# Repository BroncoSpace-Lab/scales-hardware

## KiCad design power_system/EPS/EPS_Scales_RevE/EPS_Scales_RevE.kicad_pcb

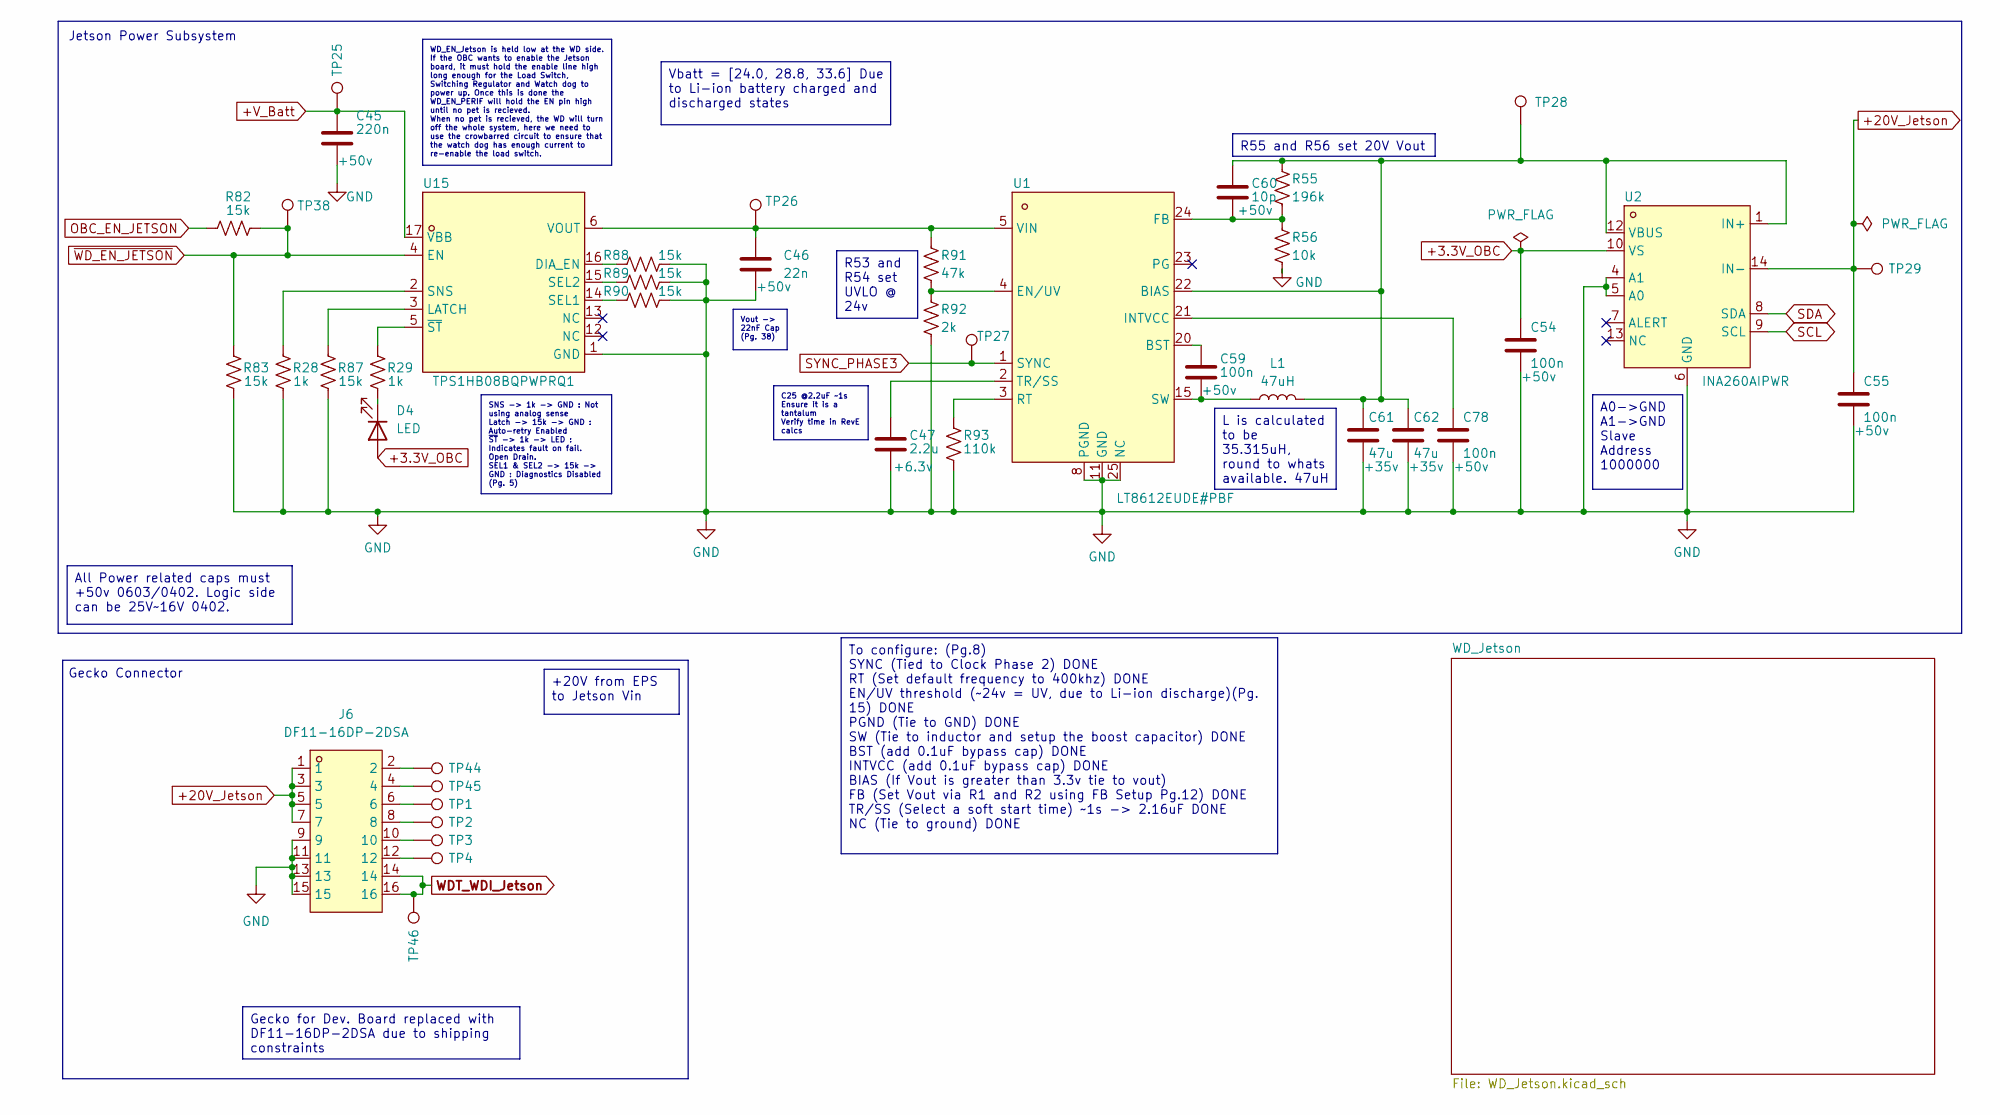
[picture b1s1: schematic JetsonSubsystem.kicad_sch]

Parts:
C45: 220n; C0402; Voltage Rating +50v; LCSC C5159775
C46: 22n; C0402; Voltage Rating +50v; LCSC C77023
C47: 2.2u; C0402; Voltage Rating +6.3v; LCSC C12530
C54, C55, C59, C78: 100n; C0402; Voltage Rating +50v; LCSC C85858
C60: 10p; C0402; Voltage Rating +50v; LCSC C1545
C61, C62: 47u; CAP-SMD_L7.3-W4.3-FD; Voltage Rating +35v; LCSC C87110
D4: LED; LED0603-RD_RED
J6: DF11-16DP-2DSA; CONN-TH_DF11-16DP-2DSA-08; LCSC Part C530981
L1: 47uH; IND-SMD_L10.7-W10.0_ETQP5MXXXX; LCSC C409637
R28, R29: 1k; R0402
R55: 196k; R0402; LCSC C2077051
R56: 10k; R0402; LCSC C25531
R82, R83, R87, R88, R89, R90: 15k; R0402; LCSC C114761
R91: 47k; R0402; LCSC C93943
R92: 2k; R0402; LCSC C60488
R93: 110k; R0402; LCSC C138065
TP1, TP2, TP3, TP4, TP25, TP26, TP27, TP28, TP29, TP38, TP44, TP45, TP46: TestPoint; TestPoint_Pad_1.0x1.0mm
U1: LT8612EUDE#PBF; QFN-28_L6.0-W3.0-P0.50-BL-EP; LCSC Part C580312
U2: INA260AIPWR; TSSOP-16_L5.0-W4.4-P0.65-LS6.4-BL-1; LCSC Part C2155885
U15: TPS1HB08BQPWPRQ1; HTSSOP-16_L5.0-W4.4-P0.65-LS6.4-TL-EP2.9; LCSC Part C3230075

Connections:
+3.3V_OBC: C54.1, D4.2 (A), U2.10 (VS); also elsewhere on the board
+20V_Jetson: C55.1, J6.1, J6.3, J6.5, J6.7, TP29.1, U2.14 (IN-); also elsewhere on the board
+V_Batt: C45.1, TP25.1, U15.17 (VBB); also elsewhere on the board
GND: C45.2, C46.2, C47.2, C54.2, C55.2, C61.2, C62.2, C78.2, J6.9, J6.11, J6.13, J6.15, R28.1, R56.2, R83.2, R87.2, R88.2, R89.2, R90.2, R92.2, R93.2, U1.8 (PGND), U1.11 (GND), U1.25 (NC), U2.4 (A1), U2.5 (A0), U2.6 (GND), U15.1 (GND); also elsewhere on the board
unnamed: D4.1 (K), R29.1
unnamed: J6.2, TP44.1
unnamed: J6.4, TP45.1
unnamed: J6.6, TP1.1
unnamed: J6.8, TP2.1
unnamed: J6.10, TP3.1
unnamed: J6.12, TP4.1
unnamed: C60.1, C61.1, C62.1, L1.2, R55.1, TP28.1, U1.22 (BIAS), U2.1 (IN+), U2.12 (VBUS)
unnamed: C59.1, U1.20 (BST)
unnamed: R91.2, R92.1, U1.4 (EN/UV)
unnamed: C60.2, R55.2, R56.1, U1.24 (FB)
unnamed: C78.1, U1.21 (INTVCC)
unnamed: R93.1, U1.3 (RT)
unnamed: C59.2, L1.1, U1.15 (SW)
unnamed: C47.1, U1.2 (TR/SS)
unnamed: C46.1, R91.1, TP26.1, U1.5 (VIN), U15.6 (VOUT)
unnamed: R88.1, U15.16 (DIA_EN)
unnamed: R87.1, U15.3 (LATCH)
unnamed: R90.1, U15.14 (SEL1)
unnamed: R89.1, U15.15 (SEL2)
unnamed: R28.2, U15.2 (SNS)
unnamed: R29.2, U15.5 (~ST)
OBC_EN_JETSON: R82.2; also elsewhere on the board
SCL: U2.9 (SCL); also elsewhere on the board
SDA: U2.8 (SDA); also elsewhere on the board
SYNC_PHASE3: TP27.1, U1.1 (SYNC); also elsewhere on the board
WDT_WDI_Jetson: J6.14, J6.16, TP46.1; also elsewhere on the board
~WD_EN_JETSON: R82.1, R83.1, TP38.1, U15.4 (EN); also elsewhere on the board

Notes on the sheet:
Jetson Power Subsystem
Gecko Connector
Gecko for Dev. Board replaced with DF11-16DP-2DSA due to shipping constraints
C25 @2.2uF ~1s Ensure it is a tantalum Verify time in RevE calcs
To configure: (Pg.8) SYNC (Tied to Clock Phase 2) DONE RT (Set default frequency to 400khz) DONE EN/UV threshold (~24v = UV, due to Li-ion discharge)(Pg. 15) DONE PGND (Tie to GND) DONE SW (Tie to inductor and setup the boost capacitor) DONE BST (add 0.1uF bypass cap) DONE INTVCC (add 0.1uF bypass 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
SNS -> 1k -> GND : Not using analog sense Latch -> 15k -> GND : Auto-retry Enabled ~{ST} -> 1k -> LED : Indicates fault on fail. Open Drain. SEL1 & SEL2 -> 15k -> GND : Diagnostics Disabled (Pg. 5)
R53 and R54 set UVLO @ 24v
R55 and R56 set 20V Vout
A0->GND A1->GND Slave Address 1000000
Vout -> 22nF Cap (Pg. 38)
Vbatt = [24.0, 28.8, 33.6] Due to Li-ion battery charged and discharged states
WD_EN_Jetson is held low at the WD side. If the OBC wants to enable the Jetson board, it must hold the enable line high long enough for the Load Switch, Switching Regulator and Watch dog to power up. Once this is done the WD_EN_PERIF will hold the EN pin high until no pet is recieved. When no pet i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
All Power related caps must +50v 0603/0402. Logic side can be 25V~16V 0402.
L is calculated to be 35.315uH, round to whats available. 47uH
+20V from EPS to Jetson Vin

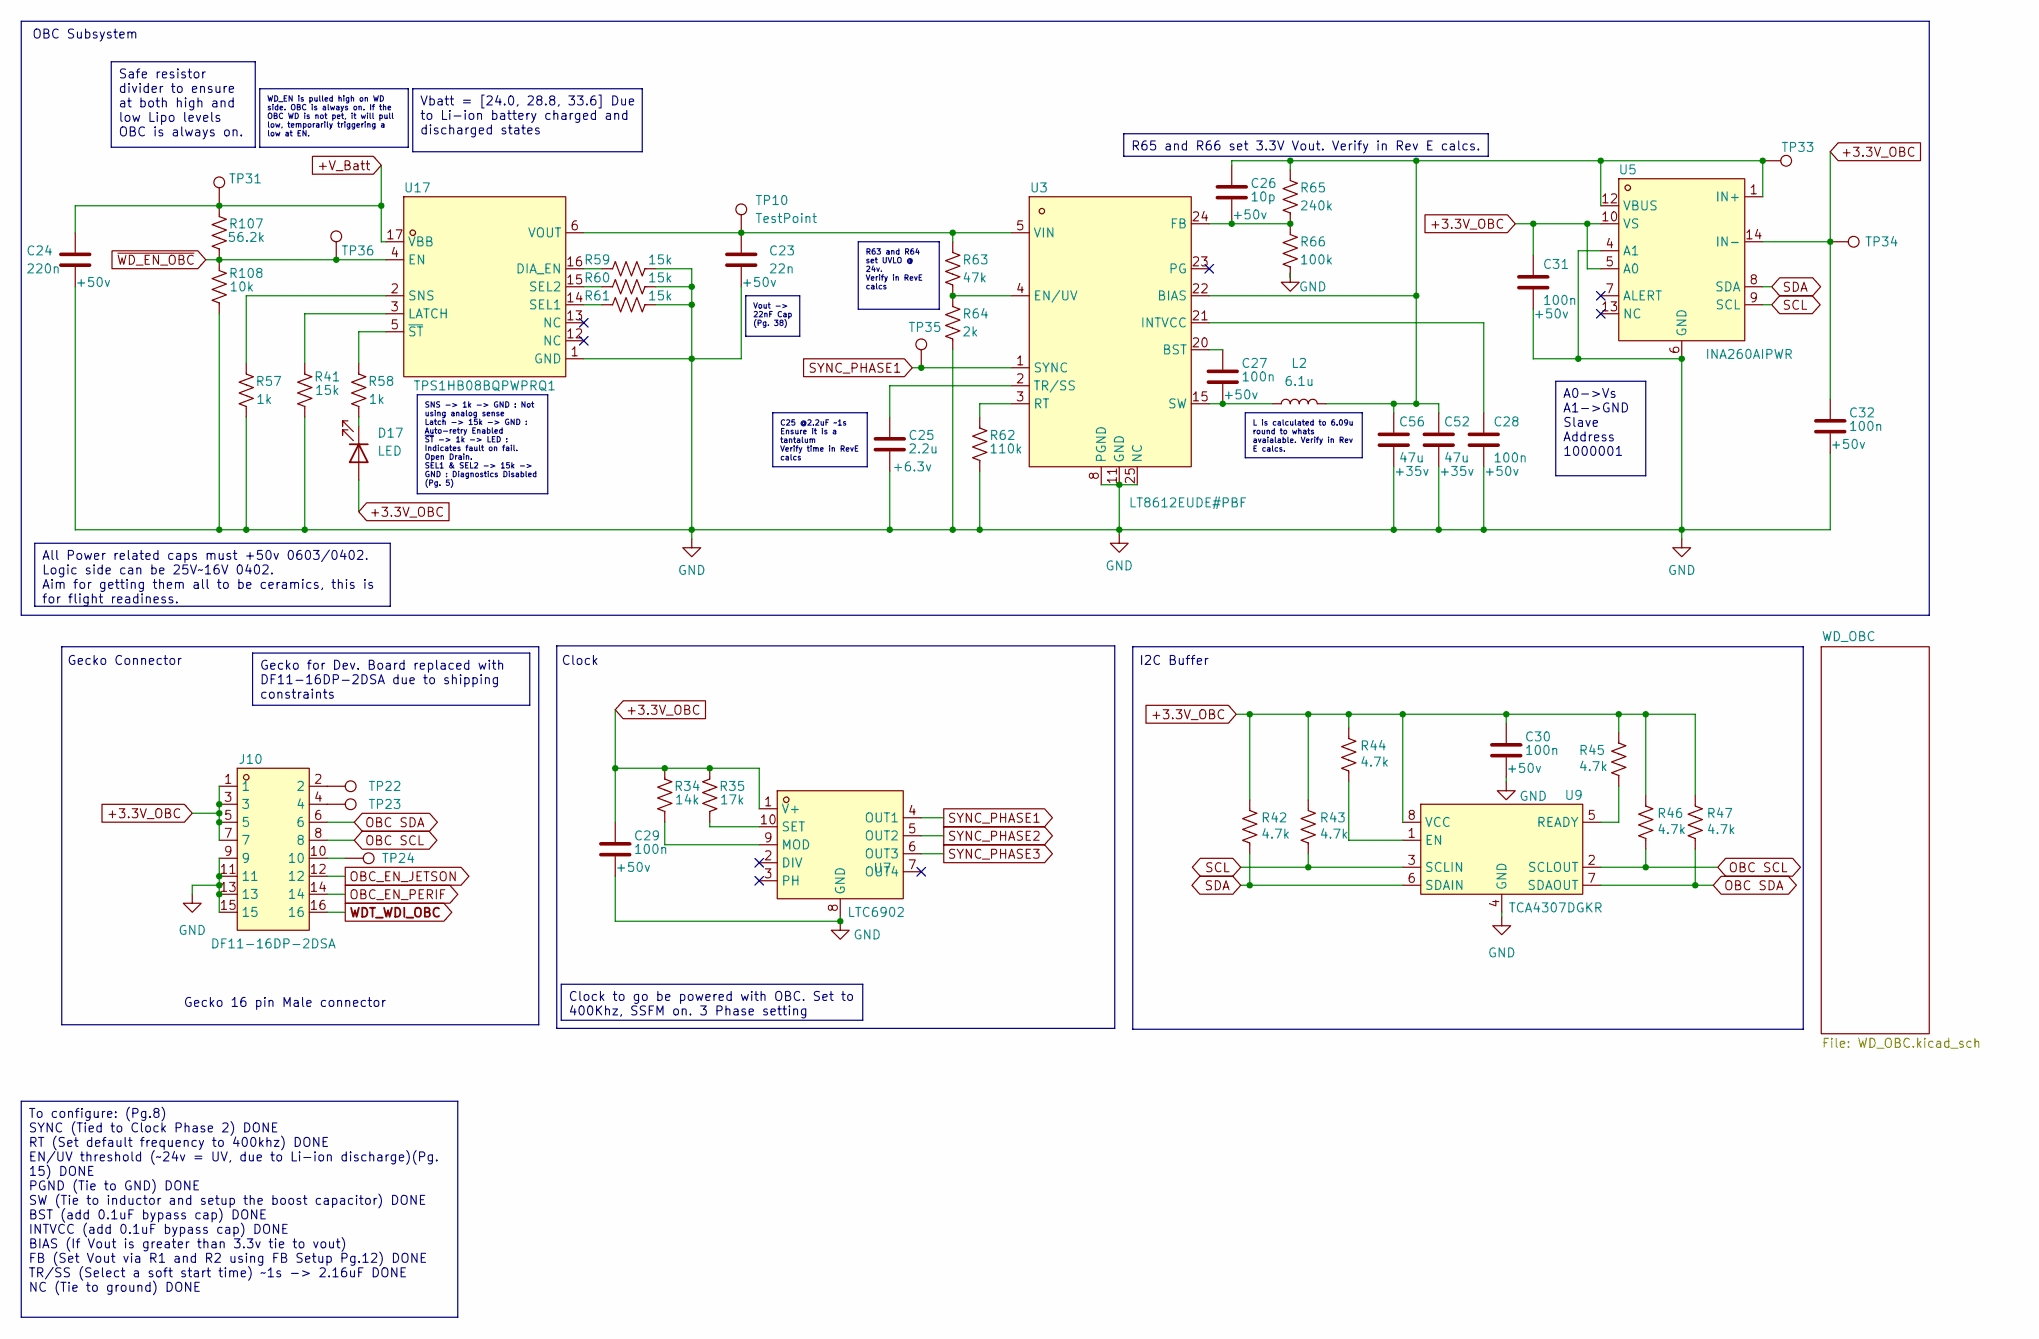
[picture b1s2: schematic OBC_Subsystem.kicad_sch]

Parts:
C23: 22n; C0402; Voltage Rating +50v; LCSC C77023
C24: 220n; C0402; Voltage Rating +50v; LCSC C5159775
C25: 2.2u; C0402; Voltage Rating +6.3v; LCSC C12530
C26: 10p; C0402; Voltage Rating +50v; LCSC C1545
C27, C28, C29, C30, C31, C32: 100n; C0402; Voltage Rating +50v; LCSC C85858
C52, C56: 47u; CAP-SMD_L7.3-W4.3-FD; Voltage Rating +35v; LCSC C87110
D17: LED; LED0603-RD_RED; LCSC C2286
J10: DF11-16DP-2DSA; CONN-TH_DF11-16DP-2DSA-08; LCSC Part C530981
L2: 6.1u; IND-SMD_FTKB1207-6R1NT; LCSC C3040409
R34: 14k; R_0603_1608Metric; LCSC C2930066
R35: 17k; R_0603_1608Metric; LCSC C137788
R41: 15k; R0402; LCSC C114761
R42, R43, R44, R45, R46, R47: 4.7k; R_0603_1608Metric; LCSC C99782
R57, R58: 1k; R0402; LCSC C106235
R59, R60, R61: 15k; R0402; LCSC C25756
R62: 110k; R0402; LCSC C138065
R63: 47k; R0402; LCSC C93943
R64: 2k; R0402; LCSC C60488
R65: 240k; R0402; LCSC C138029
R66: 100k; R0402; LCSC C60491
R107: 56.2k; R0402; LCSC C54968
R108: 10k; R0402; LCSC C25531
TP10, TP22, TP23, TP24, TP31, TP33, TP34, TP35, TP36: TestPoint; TestPoint_Pad_1.0x1.0mm
U3: LT8612EUDE#PBF; QFN-28_L6.0-W3.0-P0.50-BL-EP; LCSC Part C580312
U5: INA260AIPWR; TSSOP-16_L5.0-W4.4-P0.65-LS6.4-BL-1; LCSC Part C2155885
U7: LTC6902; MSOP-10_L3.0-W3.0-P0.50-LS5.0-BL; LCSC C581012
U9: TCA4307DGKR; VSSOP-8_L3.0-W3.0-P0.65-LS4.9-BL; LCSC Part C880333
U17: TPS1HB08BQPWPRQ1; HTSSOP-16_L5.0-W4.4-P0.65-LS6.4-TL-EP2.9; LCSC Part C3230075

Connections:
+3.3V_OBC: C29.1, C30.1, C31.1, C32.1, D17.2 (A), J10.1, J10.3, J10.5, J10.7, R34.1, R35.1, R42.1, R43.1, R44.1, R45.1, R46.1, R47.1, TP34.1, U5.5 (A0), U5.10 (VS), U5.14 (IN-), U7.1 (V+), U9.8 (VCC); also elsewhere on the board
+V_Batt: C24.1, R107.2, TP31.1, U17.17 (VBB); also elsewhere on the board
GND: C23.2, C24.2, C25.2, C28.2, C29.2, C30.2, C31.2, C32.2, C52.2, C56.2, J10.9, J10.11, J10.13, J10.15, R41.1, R57.1, R59.2, R60.2, R61.2, R62.2, R64.2, R66.2, R108.1, U3.8 (PGND), U3.11 (GND), U3.25 (NC), U5.4 (A1), U5.6 (GND), U7.8 (GND), U9.4 (GND), U17.1 (GND); also elsewhere on the board
unnamed: D17.1 (K), R58.1
unnamed: J10.2, TP22.1
unnamed: J10.4, TP23.1
unnamed: J10.10, TP24.1
unnamed: C26.1, C52.1, C56.1, L2.2, R65.1, TP33.1, U3.22 (BIAS), U5.1 (IN+), U5.12 (VBUS)
unnamed: C27.1, U3.20 (BST)
unnamed: R63.2, R64.1, U3.4 (EN/UV)
unnamed: C26.2, R65.2, R66.1, U3.24 (FB)
unnamed: C28.1, U3.21 (INTVCC)
unnamed: R62.1, U3.3 (RT)
unnamed: C27.2, L2.1, U3.15 (SW)
unnamed: C25.1, U3.2 (TR/SS)
unnamed: R34.2, U7.9 (MOD)
unnamed: R35.2, U7.10 (SET)
unnamed: R44.2, U9.1 (EN)
unnamed: R45.2, U9.5 (READY)
unnamed: R59.1, U17.16 (DIA_EN)
unnamed: R41.2, U17.3 (LATCH)
unnamed: R61.1, U17.14 (SEL1)
unnamed: R60.1, U17.15 (SEL2)
unnamed: R57.2, U17.2 (SNS)
unnamed: C23.1, R63.1, TP10.1, U3.5 (VIN), U17.6 (VOUT)
unnamed: R58.2, U17.5 (~ST)
OBC SCL: J10.8, R46.2, U9.2 (SCLOUT)
OBC SDA: J10.6, R47.2, U9.7 (SDAOUT)
OBC_EN_JETSON: J10.12; also elsewhere on the board
OBC_EN_PERIF: J10.14; also elsewhere on the board
SCL: R43.2, U5.9 (SCL), U9.3 (SCLIN); also elsewhere on the board
SDA: R42.2, U5.8 (SDA), U9.6 (SDAIN); also elsewhere on the board
SYNC_PHASE1: TP35.1, U3.1 (SYNC), U7.4 (OUT1)
SYNC_PHASE2: U7.5 (OUT2); also elsewhere on the board
SYNC_PHASE3: U7.6 (OUT3); also elsewhere on the board
WDT_WDI_OBC: J10.16; also elsewhere on the board
~WD_EN_OBC: R107.1, R108.2, TP36.1, U17.4 (EN); also elsewhere on the board

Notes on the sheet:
Clock
OBC Subsystem
I2C Buffer
Gecko Connector
Gecko 16 pin Male connector
R65 and R66 set 3.3V Vout. Verify in Rev E calcs.
L is calculated to 6.09u round to whats avaialable. Verify in Rev E calcs.
A0->Vs A1->GND Slave Address 1000001
All Power related caps must +50v 0603/0402. Logic side can be 25V~16V 0402. Aim for getting them all to be ceramics, this is for flight readiness.
To configure: (Pg.8) SYNC (Tied to Clock Phase 2) DONE RT (Set default frequency to 400khz) DONE EN/UV threshold (~24v = UV, due to Li-ion discharge)(Pg. 15) DONE PGND (Tie to GND) DONE SW (Tie to inductor and setup the boost capacitor) DONE BST (add 0.1uF bypass cap) DONE INTVCC (add 0.1uF bypass 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
Vbatt = [24.0, 28.8, 33.6] Due to Li-ion battery charged and discharged states
Safe resistor divider to ensure at both high and low Lipo levels OBC is always on.
WD_EN is pulled high on WD side. OBC is always on. If the OBC WD is not pet, it will pull low, temporarily triggering a low at EN.
R63 and R64 set UVLO @ 24v. Verify in RevE calcs
Vout -> 22nF Cap (Pg. 38)
C25 @2.2uF ~1s Ensure it is a tantalum Verify time in RevE calcs
Gecko for Dev. Board replaced with DF11-16DP-2DSA due to shipping constraints
SNS -> 1k -> GND : Not using analog sense Latch -> 15k -> GND : Auto-retry Enabled ~{ST} -> 1k -> LED : Indicates fault on fail. Open Drain. SEL1 & SEL2 -> 15k -> GND : Diagnostics Disabled (Pg. 5)
Clock to go be powered with OBC. Set to 400Khz, SSFM on. 3 Phase setting

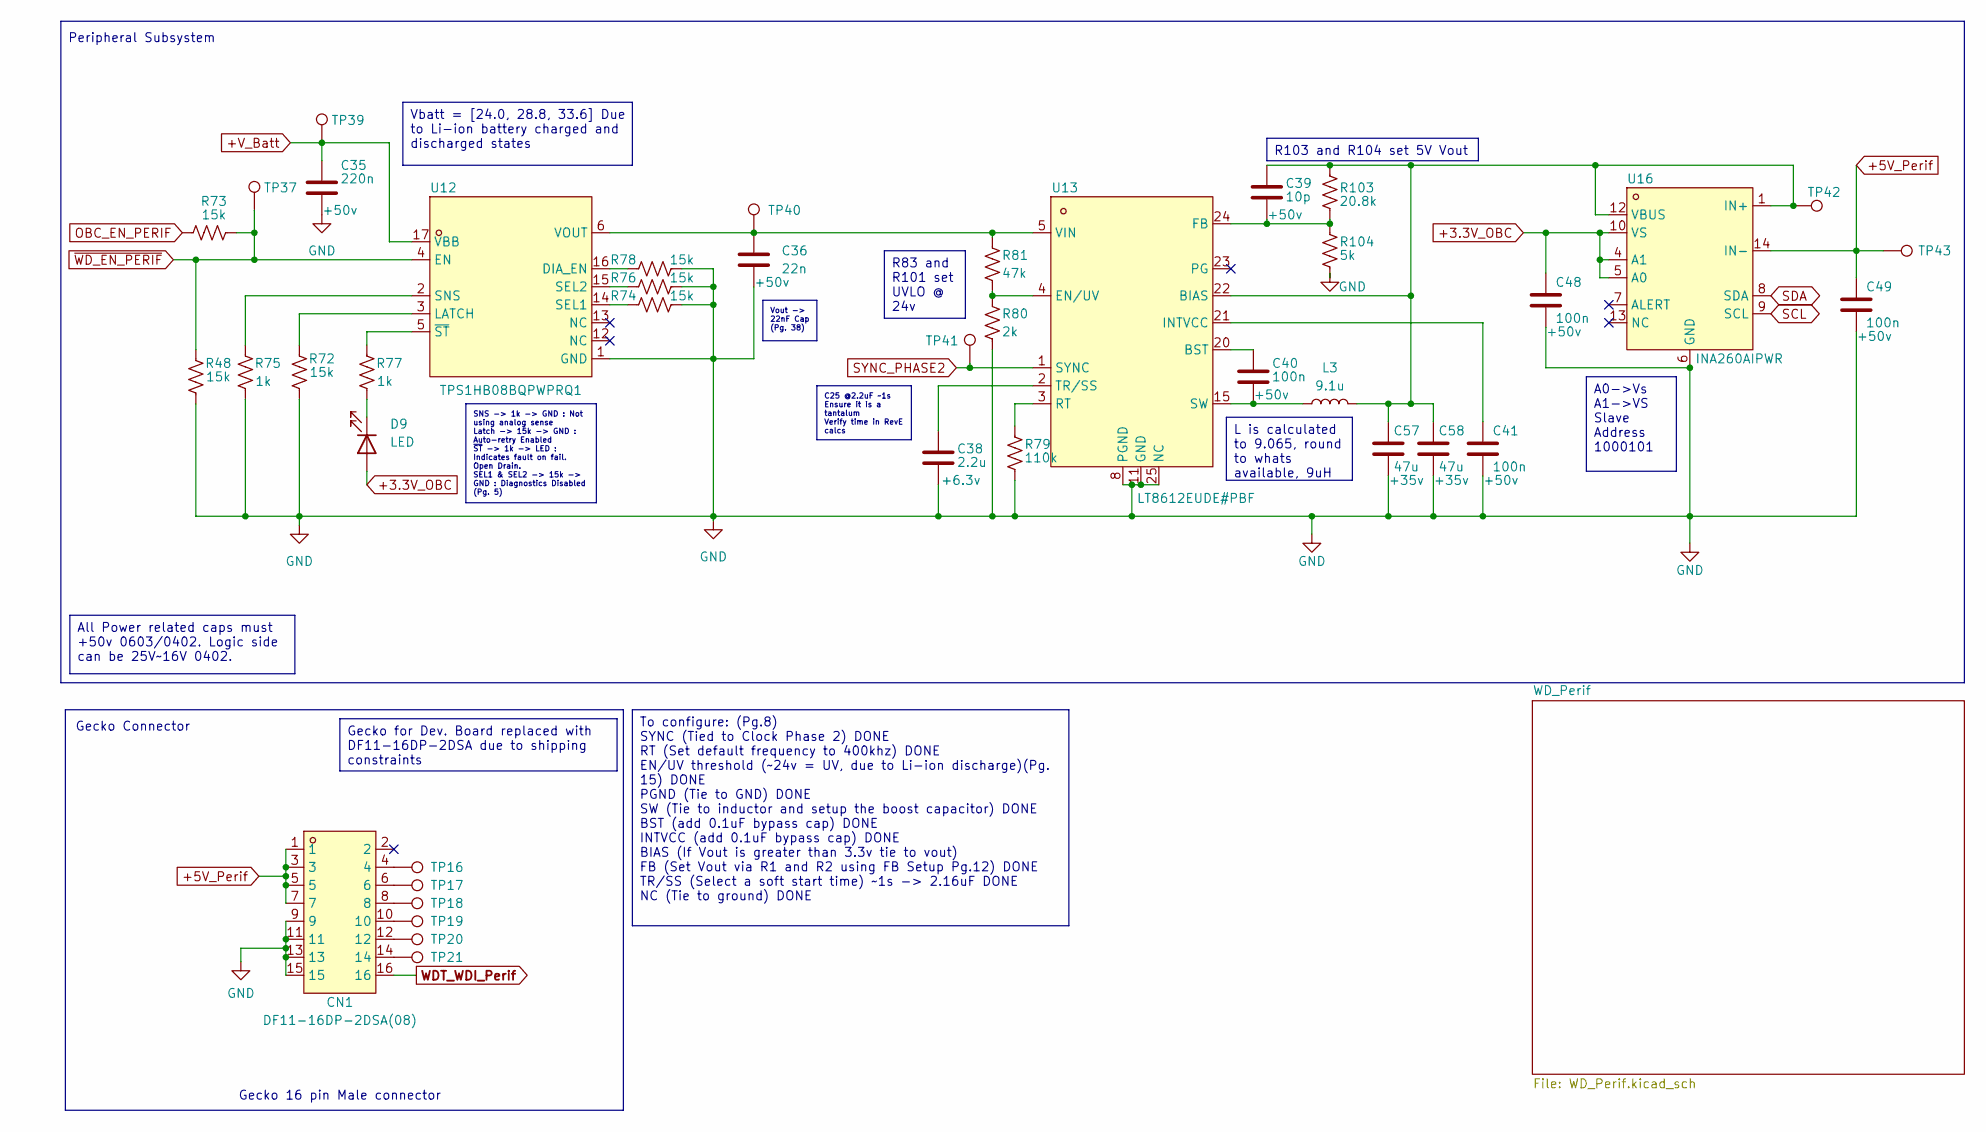
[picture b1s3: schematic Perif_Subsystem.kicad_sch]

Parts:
C35: 220n; C0402; Voltage Rating +50v; LCSC C5159775
C36: 22n; C0402; Voltage Rating +50v; LCSC C77023
C38: 2.2u; C0402; Voltage Rating +6.3v; LCSC C12530
C39: 10p; C0402; Voltage Rating +50v; LCSC C1545
C40, C41, C48, C49: 100n; C0402; Voltage Rating +50v; LCSC C85858
C57, C58: 47u; CAP-SMD_L7.3-W4.3-FD; Voltage Rating +35v; LCSC C87110
CN1: DF11-16DP-2DSA(08); CONN-TH_DF11-16DP-2DSA-08; LCSC Part C530981
D9: LED; LED0603-RD_RED
L3: 9.1u; IND-SMD_L6.0-W6.0_ASPI-6045S; LCSC C187449
R48, R72, R73, R74, R76, R78: 15k; R0402; LCSC C114761
R75, R77: 1k; R0402; LCSC C106235
R79: 110k; R0402; LCSC C138065
R80: 2k; R0402; LCSC C60488
R81: 47k; R0402; LCSC C93943
R103: 20.8k; R0402; LCSC C25766
R104: 5k; R0402; LCSC C477765
TP16, TP17, TP18, TP19, TP20, TP21, TP37, TP39, TP40, TP41, TP42, TP43: TestPoint; TestPoint_Pad_1.0x1.0mm
U12: TPS1HB08BQPWPRQ1; HTSSOP-16_L5.0-W4.4-P0.65-LS6.4-TL-EP2.9; LCSC Part C3230075
U13: LT8612EUDE#PBF; QFN-28_L6.0-W3.0-P0.50-BL-EP; LCSC Part C580312
U16: INA260AIPWR; TSSOP-16_L5.0-W4.4-P0.65-LS6.4-BL-1; LCSC Part C2155885

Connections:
+3.3V_OBC: C48.1, D9.2 (A), U16.4 (A1), U16.5 (A0), U16.10 (VS); also elsewhere on the board
+5V_Perif: C49.1, CN1.1, CN1.3, CN1.5, CN1.7, TP43.1, U16.14 (IN-); also elsewhere on the board
+V_Batt: C35.1, TP39.1, U12.17 (VBB); also elsewhere on the board
GND: C35.2, C36.2, C38.2, C41.2, C48.2, C49.2, C57.2, C58.2, CN1.9, CN1.11, CN1.13, CN1.15, R48.1, R72.1, R74.1, R75.1, R76.1, R78.1, R79.2, R80.2, R104.2, U12.1 (GND), U13.8 (PGND), U13.11 (GND), U13.25 (NC), U16.6 (GND); also elsewhere on the board
unnamed: CN1.4, TP16.1
unnamed: CN1.6, TP17.1
unnamed: CN1.8, TP18.1
unnamed: CN1.10, TP19.1
unnamed: CN1.12, TP20.1
unnamed: CN1.14, TP21.1
unnamed: D9.1 (K), R77.1
unnamed: R78.2, U12.16 (DIA_EN)
unnamed: R72.2, U12.3 (LATCH)
unnamed: R74.2, U12.14 (SEL1)
unnamed: R76.2, U12.15 (SEL2)
unnamed: R75.2, U12.2 (SNS)
unnamed: C36.1, R81.1, TP40.1, U12.6 (VOUT), U13.5 (VIN)
unnamed: R77.2, U12.5 (~ST)
unnamed: C39.1, C57.1, C58.1, L3.2, R103.1, TP42.1, U13.22 (BIAS), U16.1 (IN+), U16.12 (VBUS)
unnamed: C40.1, U13.20 (BST)
unnamed: R80.1, R81.2, U13.4 (EN/UV)
unnamed: C39.2, R103.2, R104.1, U13.24 (FB)
unnamed: C41.1, U13.21 (INTVCC)
unnamed: R79.1, U13.3 (RT)
unnamed: C40.2, L3.1, U13.15 (SW)
unnamed: C38.1, U13.2 (TR/SS)
OBC_EN_PERIF: R73.2; also elsewhere on the board
SCL: U16.9 (SCL); also elsewhere on the board
SDA: U16.8 (SDA); also elsewhere on the board
SYNC_PHASE2: TP41.1, U13.1 (SYNC); also elsewhere on the board
WDT_WDI_Perif: CN1.16; also elsewhere on the board
~WD_EN_PERIF: R48.2, R73.1, TP37.1, U12.4 (EN); also elsewhere on the board

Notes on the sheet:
Gecko 16 pin Male connector
Peripheral Subsystem
Gecko Connector
C25 @2.2uF ~1s Ensure it is a tantalum Verify time in RevE calcs
A0->Vs A1->VS Slave Address 1000101
To configure: (Pg.8) SYNC (Tied to Clock Phase 2) DONE RT (Set default frequency to 400khz) DONE EN/UV threshold (~24v = UV, due to Li-ion discharge)(Pg. 15) DONE PGND (Tie to GND) DONE SW (Tie to inductor and setup the boost capacitor) DONE BST (add 0.1uF bypass cap) DONE INTVCC (add 0.1uF bypass 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
R103 and R104 set 5V Vout
L is calculated to 9.065, round to whats available, 9uH
Vbatt = [24.0, 28.8, 33.6] Due to Li-ion battery charged and discharged states
R83 and R101 set UVLO @ 24v
Vout -> 22nF Cap (Pg. 38)
Gecko for Dev. Board replaced with DF11-16DP-2DSA due to shipping constraints
All Power related caps must +50v 0603/0402. Logic side can be 25V~16V 0402.
SNS -> 1k -> GND : Not using analog sense Latch -> 15k -> GND : Auto-retry Enabled ~{ST} -> 1k -> LED : Indicates fault on fail. Open Drain. SEL1 & SEL2 -> 15k -> GND : Diagnostics Disabled (Pg. 5)

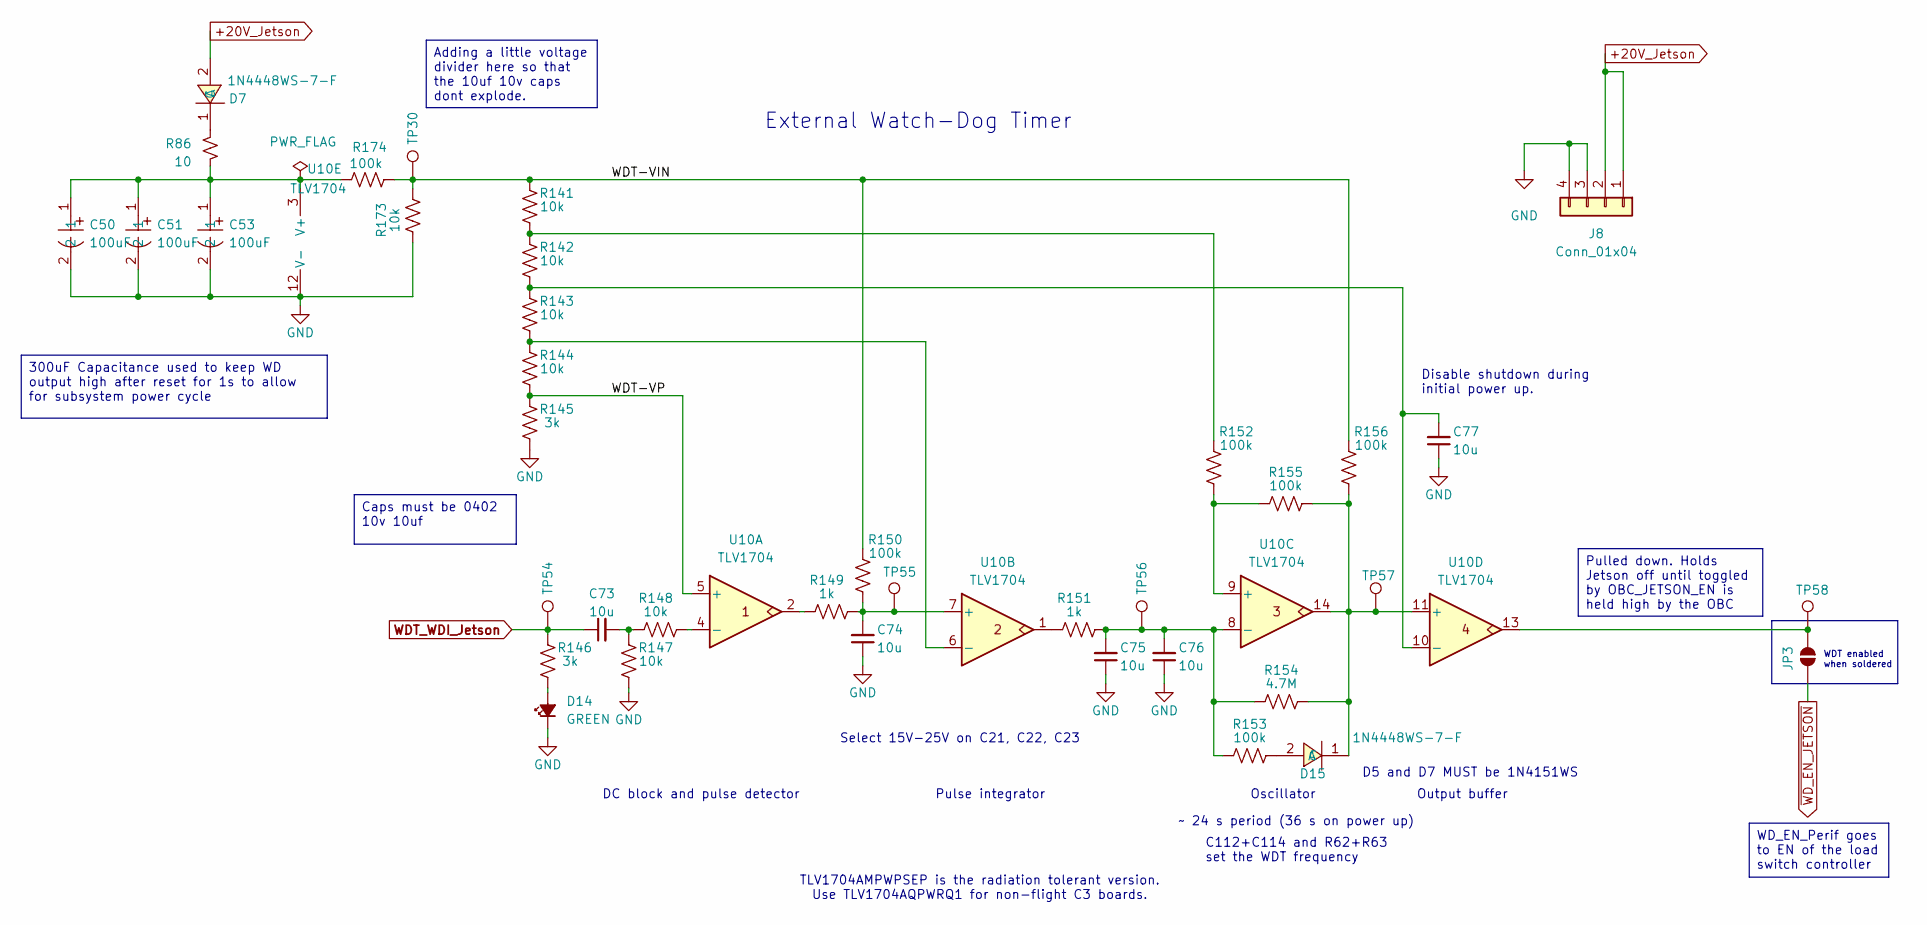
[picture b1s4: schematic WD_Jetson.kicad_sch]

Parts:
C50, C51, C53: 100uF; CAP-SMD_L7.3-W6.1_TCN4227M025R0100; LCSC Part C2158793
C73, C76, C77: 10u; C0402; LCSC 194427
C74, C75: 10u; C0402
D7, D15: 1N4448WS-7-F; SOD-323_L1.8-W1.3-LS2.5-RD; MPN 1N4151WS-E3-08; LCSC C2979762
D14: GREEN; LED_0603_1608Metric; MPN 150060GS75000; LCSC C965799
J8: Conn_01x04; PinSocket_1x04_P2.54mm_Vertical
JP3: SolderJumper_2_Open; SolderJumper-2_P1.3mm_Open_RoundedPad1.0x1.5mm
R86: 10; R_1206_3216Metric; MPN ESR18EZPF10R0; LCSC C17903
R141, R142, R143, R144, R147, R148, R173: 10k; R0402; LCSC C25531
R145, R146: 3k; R0402; LCSC C2909355
R149, R151: 1k; R0402; LCSC C106235
R150, R152, R153, R155, R156, R174: 100k; R0402; LCSC C269673
R154: 4.7M; R0402; LCSC C474132
TP30, TP54, TP55, TP56, TP57, TP58: TestPoint; TestPoint_Pad_1.0x1.0mm
U10: TLV1704; TSSOP-14_4.4x5mm_P0.65mm; MPN TLV1704AQPWRQ1; LCSC C181596

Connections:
+20V_Jetson: D7.2 (A), J8.1, J8.2; also elsewhere on the board
/Jetson_Subsystem/WD_Jetson/WDT-VIN: R141.2, R150.1, R156.1, R173.1, R174.2, TP30.1
/Jetson_Subsystem/WD_Jetson/WDT-VP: R144.1, R145.2, U10.5 (+)
GND: C50.2, C51.2, C53.2, C74.1, C75.1, C76.1, C77.1, D14.1 (K), J8.3, J8.4, R145.1, R147.1, R173.2, U10.12 (V-); also elsewhere on the board
unnamed: C73.2, R147.2, R148.2
unnamed: D7.1 (C), R86.1
unnamed: D14.2 (A), R146.1
unnamed: D15.2 (A), R153.2
unnamed: D15.1 (C), R154.2, R155.2, R156.2, TP57.1, U10.11 (+), U10.14
unnamed: JP3.1 (A), TP58.1, U10.13
unnamed: R141.1, R142.2, R152.1
unnamed: R149.2, U10.2
unnamed: R151.2, U10.1
unnamed: R148.1, U10.4 (-)
unnamed: C74.2, R149.1, R150.2, TP55.1, U10.7 (+)
unnamed: R143.1, R144.2, U10.6 (-)
unnamed: R152.2, R155.1, U10.9 (+)
unnamed: C75.2, C76.2, R151.1, R153.1, R154.1, TP56.1, U10.8 (-)
unnamed: C77.2, R142.1, R143.2, U10.10 (-)
unnamed: C50.1, C51.1, C53.1, R86.2, R174.1, U10.3 (V+)
WDT_WDI_Jetson: C73.1, R146.2, TP54.1; also elsewhere on the board
~WD_EN_JETSON: JP3.2 (B); also elsewhere on the board

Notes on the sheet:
Select 15V-25V on C21, C22, C23
Output buffer
~ 24 s period (36 s on power up)
Disable shutdown during initial power up.
Oscillator
Pulse integrator
DC block and pulse detector
D5 and D7 MUST be 1N4151WS
WDT enabled when soldered
External Watch-Dog Timer
TLV1704AMPWPSEP is the radiation tolerant version. Use TLV1704AQPWRQ1 for non-flight C3 boards.
C112+C114 and R62+R63 set the WDT frequency
Adding a little voltage divider here so that the 10uf 10v caps dont explode.
300uF Capacitance used to keep WD output high after reset for 1s to allow for subsystem power cycle
Caps must be 0402 10v 10uf
Pulled down. Holds Jetson off until toggled by OBC_JETSON_EN is held high by the OBC
WD_EN_Perif goes to EN of the load switch controller

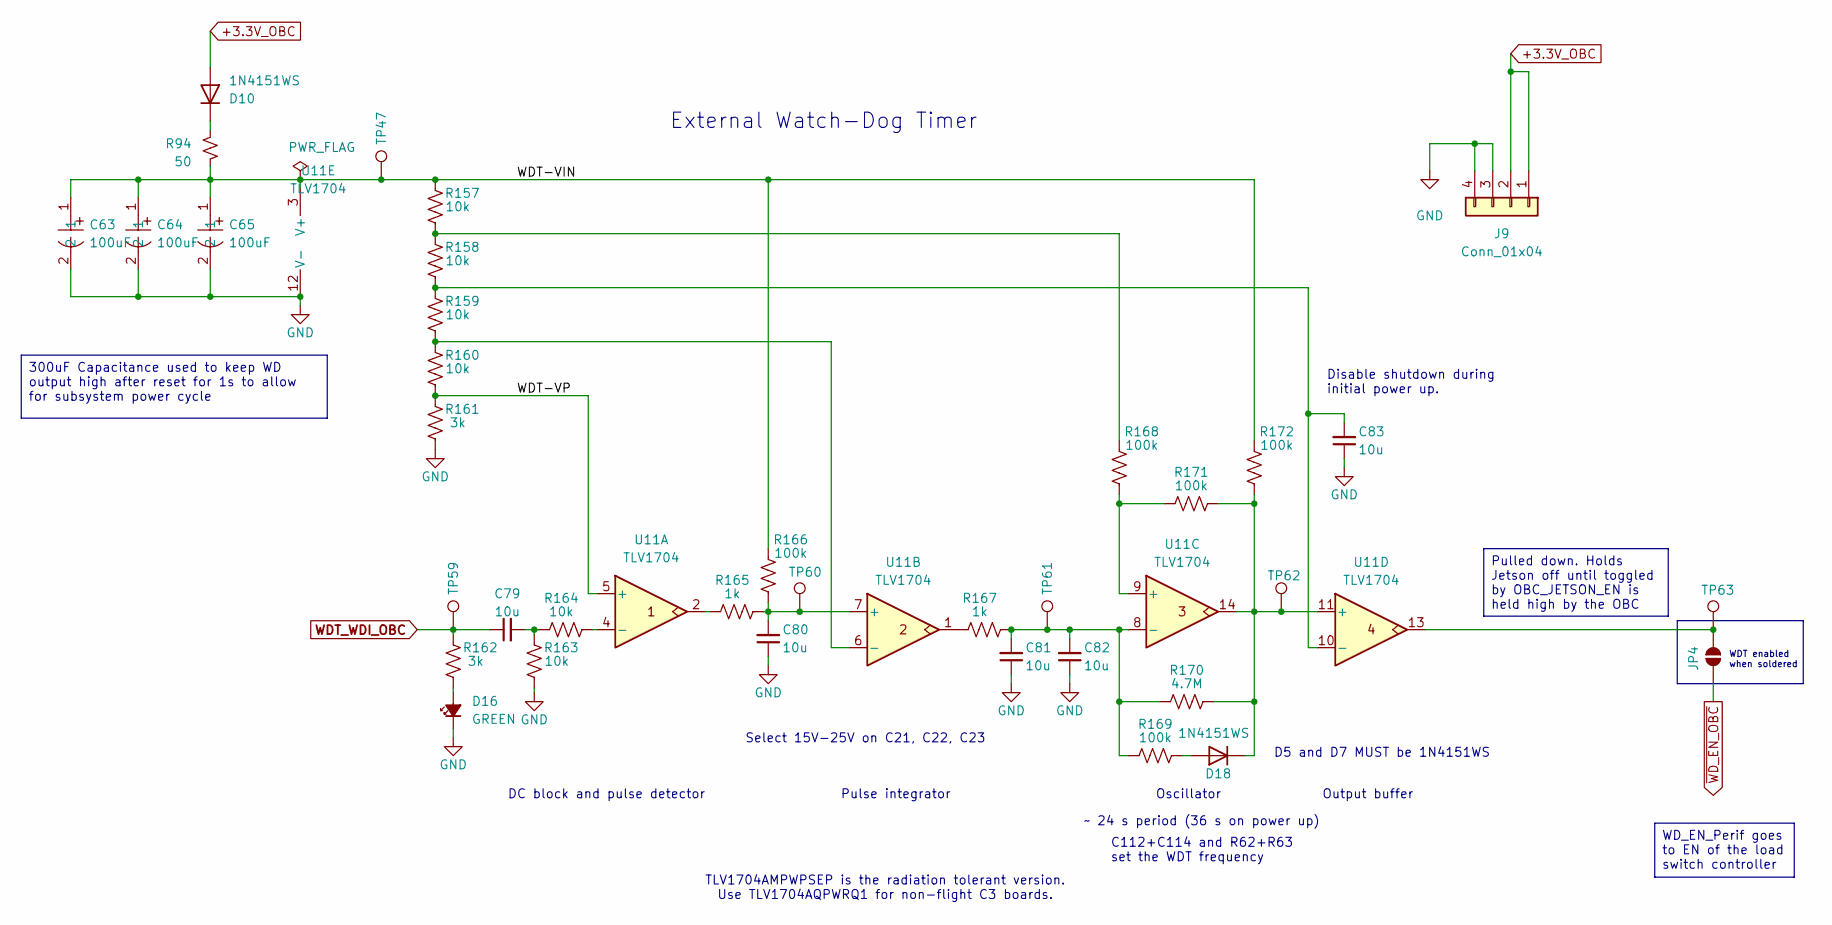
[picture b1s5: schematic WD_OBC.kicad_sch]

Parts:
C63, C64, C65: 100uF; CAP-SMD_L7.3-W6.1_TCN4227M025R0100; LCSC Part C2158793
C79, C80, C81, C82, C83: 10u; C0402; LCSC 194427
D10, D18: 1N4151WS; SOD2512X116N; MPN 1N4151WS-E3-08; LCSC C2979762
D16: GREEN; LED_0603_1608Metric; MPN 150060GS75000; LCSC C965799
J9: Conn_01x04; PinSocket_1x04_P2.54mm_Vertical
JP4: SolderJumper_2_Open; SolderJumper-2_P1.3mm_Open_RoundedPad1.0x1.5mm
R94: 50; R_1206_3216Metric; MPN ESR18EZPF10R0; LCSC C17903
R157, R158, R159, R160, R163, R164: 10k; R0402; LCSC C25531
R161, R162: 3k; R0402; LCSC C2909355
R165, R167: 1k; R0402; LCSC C106235
R166, R168, R169, R171, R172: 100k; R0402; LCSC C269673
R170: 4.7M; R0402; LCSC C474132
TP47, TP59, TP60, TP61, TP62, TP63: TestPoint; TestPoint_Pad_1.0x1.0mm
U11: TLV1704; TSSOP-14_4.4x5mm_P0.65mm; MPN TLV1704AQPWRQ1; LCSC C181596

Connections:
+3.3V_OBC: D10.2 (A), J9.1, J9.2; also elsewhere on the board
/OBC_Subsystem/WD_OBC/WDT-VIN: C63.1, C64.1, C65.1, R94.2, R157.2, R166.1, R172.1, TP47.1, U11.3 (V+)
/OBC_Subsystem/WD_OBC/WDT-VP: R160.1, R161.2, U11.5 (+)
GND: C63.2, C64.2, C65.2, C80.1, C81.1, C82.1, C83.1, D16.1 (K), J9.3, J9.4, R161.1, R163.1, U11.12 (V-); also elsewhere on the board
unnamed: C79.2, R163.2, R164.2
unnamed: D10.1 (C), R94.1
unnamed: D16.2 (A), R162.1
unnamed: D18.2 (A), R169.2
unnamed: D18.1 (C), R170.2, R171.2, R172.2, TP62.1, U11.11 (+), U11.14
unnamed: JP4.1 (A), TP63.1, U11.13
unnamed: R157.1, R158.2, R168.1
unnamed: R165.2, U11.2
unnamed: R167.2, U11.1
unnamed: R164.1, U11.4 (-)
unnamed: C80.2, R165.1, R166.2, TP60.1, U11.7 (+)
unnamed: R159.1, R160.2, U11.6 (-)
unnamed: R168.2, R171.1, U11.9 (+)
unnamed: C81.2, C82.2, R167.1, R169.1, R170.1, TP61.1, U11.8 (-)
unnamed: C83.2, R158.1, R159.2, U11.10 (-)
WDT_WDI_OBC: C79.1, R162.2, TP59.1; also elsewhere on the board
~WD_EN_OBC: JP4.2 (B); also elsewhere on the board

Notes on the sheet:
External Watch-Dog Timer
Disable shutdown during initial power up.
~ 24 s period (36 s on power up)
C112+C114 and R62+R63 set the WDT frequency
Output buffer
TLV1704AMPWPSEP is the radiation tolerant version. Use TLV1704AQPWRQ1 for non-flight C3 boards.
DC block and pulse detector
Oscillator
WDT enabled when soldered
Pulse integrator
Select 15V-25V on C21, C22, C23
D5 and D7 MUST be 1N4151WS
300uF Capacitance used to keep WD output high after reset for 1s to allow for subsystem power cycle
WD_EN_Perif goes to EN of the load switch controller
Pulled down. Holds Jetson off until toggled by OBC_JETSON_EN is held high by the OBC
